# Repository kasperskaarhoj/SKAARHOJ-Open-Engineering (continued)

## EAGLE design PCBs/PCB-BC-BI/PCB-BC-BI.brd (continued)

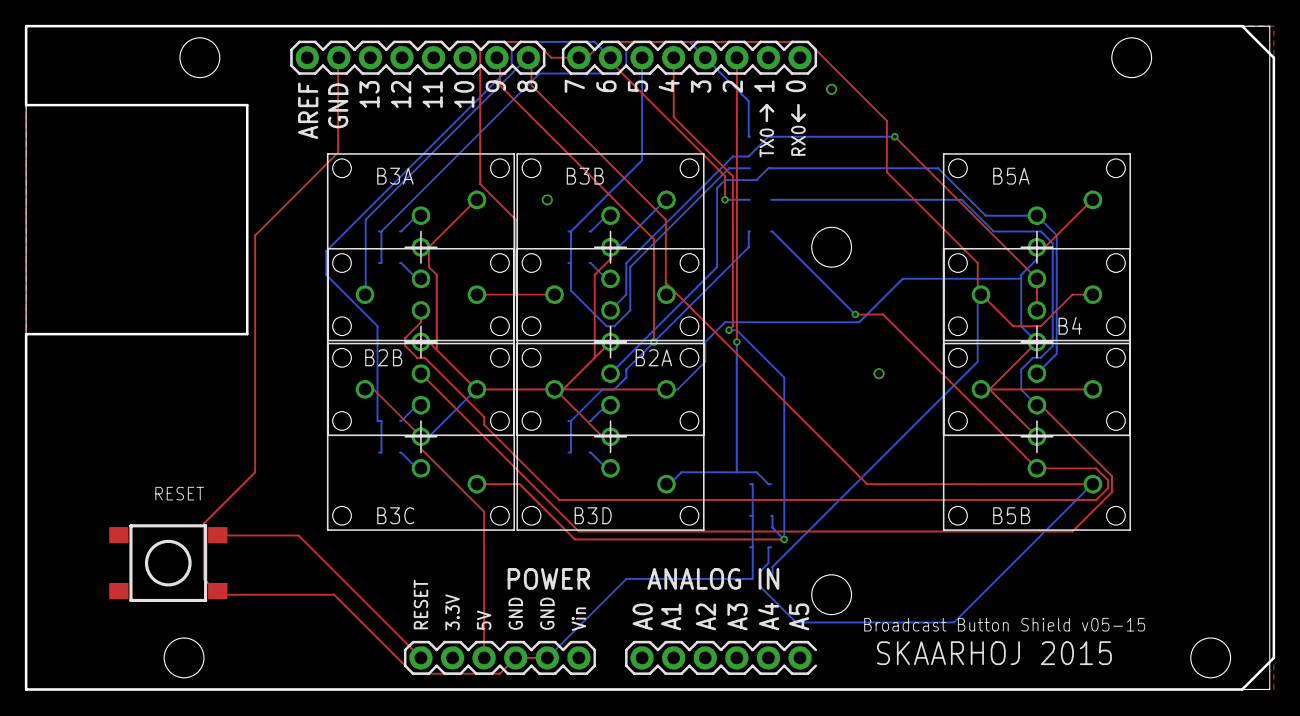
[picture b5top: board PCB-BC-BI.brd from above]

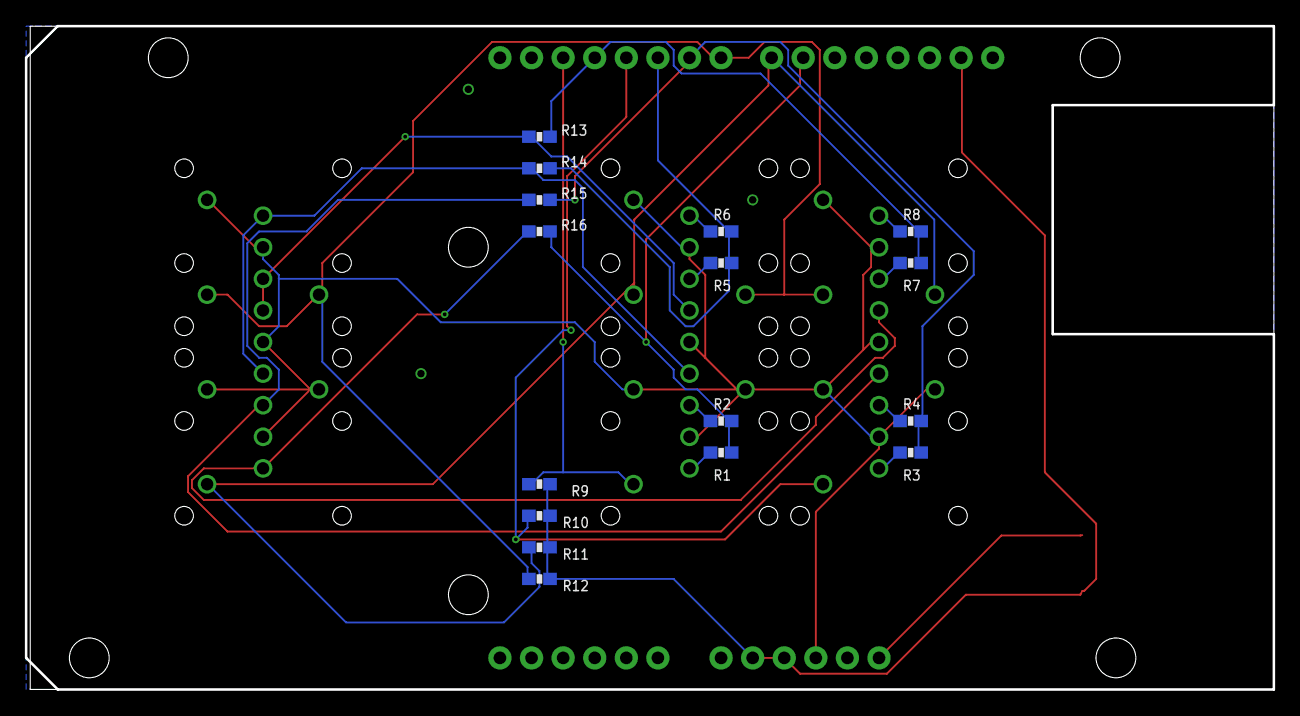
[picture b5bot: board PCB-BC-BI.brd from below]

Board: 2 copper layers, 100.3 x 53.3 mm, 27 parts (16 on the bottom side), 23 nets.

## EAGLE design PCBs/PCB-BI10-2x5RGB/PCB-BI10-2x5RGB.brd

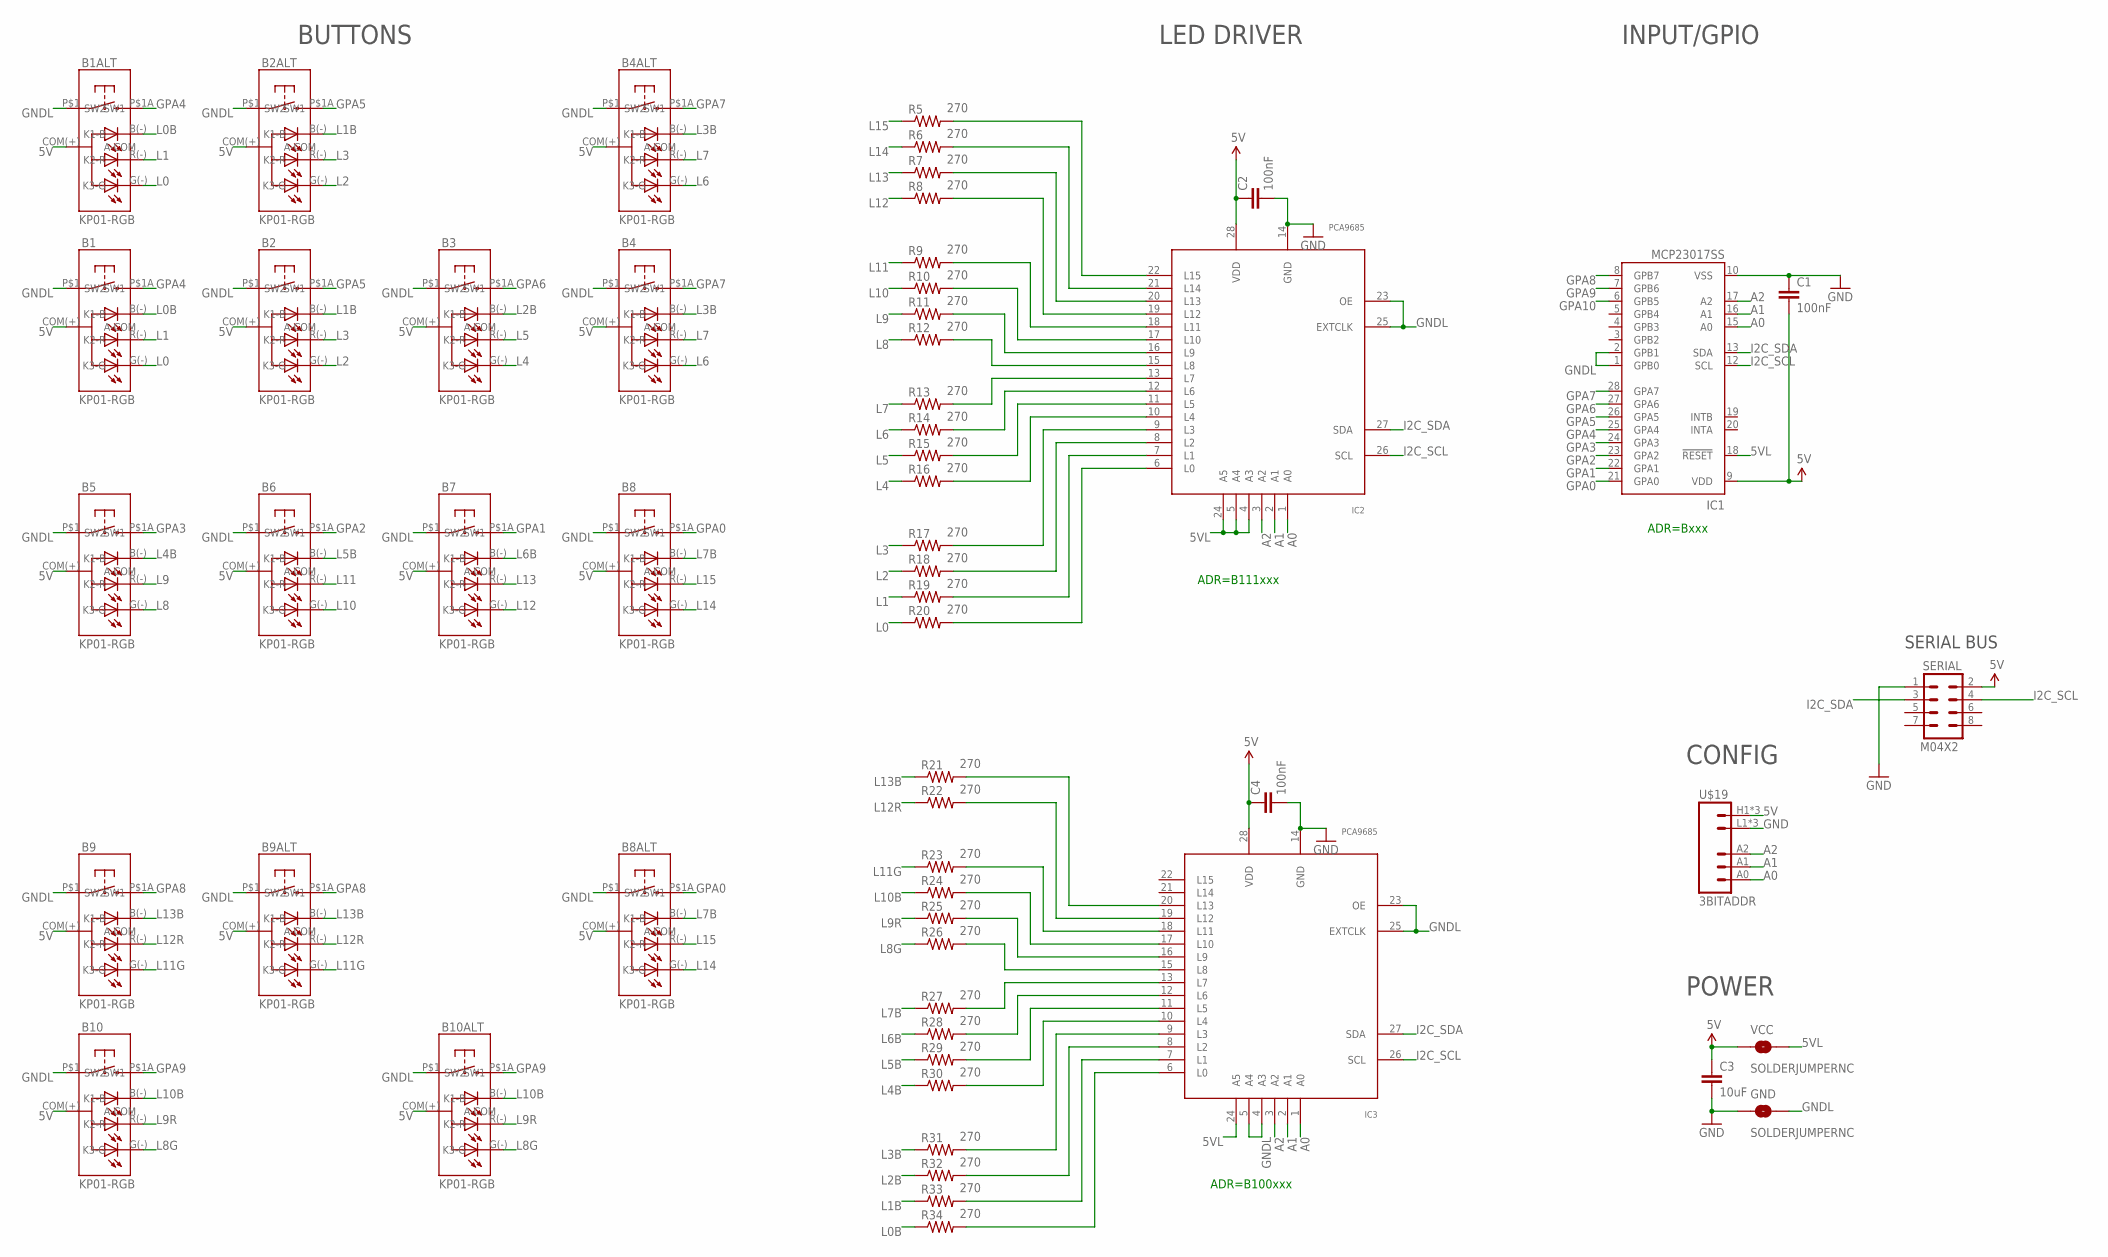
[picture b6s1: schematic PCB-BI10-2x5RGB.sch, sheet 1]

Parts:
B1, B1ALT, B2, B2ALT, B3, B4, B4ALT, B5, B6, B7, B8, B8ALT, B9, B9ALT, B10, B10ALT: KP01-RGB; NKK-KP01
C1, C2, C4: 100nF; 0603-CAP
C3: 10uF; 0805
GND: SOLDERJUMPERNC; SJ_2S
IC1: MCP23017SS; SSOP28; MPN MCP23017-E/SS
IC2, IC3: PCA9685; TSSOP28
R5, R6, R7, R8, R9, R10, R11, R12, R13, R14, R15, R16, R17, R18, R19, R20, R21, R22, R23, R24, R25, R26, R27, R28, R29, R30, R31, R32, R33, R34: 270; 0603-RES
SERIAL: M04X2; 2X4
U$19: 3BITADDR
VCC: SOLDERJUMPERNC; SJ_2S

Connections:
5V: B1.COM(+) (A-COM), B1ALT.COM(+) (A-COM), B2.COM(+) (A-COM), B2ALT.COM(+) (A-COM), B3.COM(+) (A-COM), B4.COM(+) (A-COM), B4ALT.COM(+) (A-COM), B5.COM(+) (A-COM), B6.COM(+) (A-COM), B7.COM(+) (A-COM), B8.COM(+) (A-COM), B8ALT.COM(+) (A-COM), B9.COM(+) (A-COM), B9ALT.COM(+) (A-COM), B10.COM(+) (A-COM), B10ALT.COM(+) (A-COM), C1.2, C2.1, C3.1, C4.1, IC1.9 (VDD), IC2.28 (VDD), IC3.28 (VDD), SERIAL.2, U$19.H1 (VCC), U$19.H2 (VCC), U$19.H3 (VCC), VCC.1
5VL: IC1.18 (!RESET), IC2.4 (A3), IC2.5 (A4), IC2.24 (A5), IC3.24 (A5), VCC.2
A0: IC1.15 (A0), IC2.1 (A0), IC3.1 (A0), U$19.A0
A1: IC1.16 (A1), IC2.2 (A1), IC3.2 (A1), U$19.A1
A2: IC1.17 (A2), IC2.3 (A2), IC3.3 (A2), U$19.A2
GND: C1.1, C2.2, C3.2, C4.2, GND.1, IC1.10 (VSS), IC2.14 (GND), IC3.14 (GND), SERIAL.1, U$19.L1 (GND), U$19.L2 (GND), U$19.L3 (GND)
GNDL: B1.P$1 (SW1), B1ALT.P$1 (SW1), B2.P$1 (SW1), B2ALT.P$1 (SW1), B3.P$1 (SW1), B4.P$1 (SW1), B4ALT.P$1 (SW1), B5.P$1 (SW1), B6.P$1 (SW1), B7.P$1 (SW1), B8.P$1 (SW1), B8ALT.P$1 (SW1), B9.P$1 (SW1), B9ALT.P$1 (SW1), B10.P$1 (SW1), B10ALT.P$1 (SW1), GND.2, IC1.1 (GPB0), IC1.2 (GPB1), IC2.23 (OE), IC2.25 (EXTCLK), IC3.4 (A3), IC3.5 (A4), IC3.23 (OE), IC3.25 (EXTCLK)
GPA0: B8.P$1A (SW2), B8ALT.P$1A (SW2), IC1.21 (GPA0)
GPA1: B7.P$1A (SW2), IC1.22 (GPA1)
GPA2: B6.P$1A (SW2), IC1.23 (GPA2)
GPA3: B5.P$1A (SW2), IC1.24 (GPA3)
GPA4: B1.P$1A (SW2), B1ALT.P$1A (SW2), IC1.25 (GPA4)
GPA5: B2.P$1A (SW2), B2ALT.P$1A (SW2), IC1.26 (GPA5)
GPA6: B3.P$1A (SW2), IC1.27 (GPA6)
GPA7: B4.P$1A (SW2), B4ALT.P$1A (SW2), IC1.28 (GPA7)
GPA8: B9.P$1A (SW2), B9ALT.P$1A (SW2), IC1.8 (GPB7)
GPA9: B10.P$1A (SW2), B10ALT.P$1A (SW2), IC1.7 (GPB6)
GPA10: IC1.6 (GPB5)
I2C_SCL: IC1.12 (SCL), IC2.26 (SCL), IC3.26 (SCL), SERIAL.4
I2C_SDA: IC1.13 (SDA), IC2.27 (SDA), IC3.27 (SDA), SERIAL.3
L0: B1.G(-) (K3-G), B1ALT.G(-) (K3-G), R20.1
L0B: B1.B(-) (K1-B), B1ALT.B(-) (K1-B), R34.1
L1: B1.R(-) (K2-R), B1ALT.R(-) (K2-R), R19.1
L1B: B2.B(-) (K1-B), B2ALT.B(-) (K1-B), R33.1
L2: B2.G(-) (K3-G), B2ALT.G(-) (K3-G), R18.1
L2B: B3.B(-) (K1-B), R32.1
L3: B2.R(-) (K2-R), B2ALT.R(-) (K2-R), R17.1
L3B: B4.B(-) (K1-B), B4ALT.B(-) (K1-B), R31.1
L4: B3.G(-) (K3-G), R16.1
L4B: B5.B(-) (K1-B), R30.1
L5: B3.R(-) (K2-R), R15.1
L5B: B6.B(-) (K1-B), R29.1
L6: B4.G(-) (K3-G), B4ALT.G(-) (K3-G), R14.1
L6B: B7.B(-) (K1-B), R28.1
L7: B4.R(-) (K2-R), B4ALT.R(-) (K2-R), R13.1
L7B: B8.B(-) (K1-B), B8ALT.B(-) (K1-B), R27.1
L8: B5.G(-) (K3-G), R12.1
L8G: B10.G(-) (K3-G), B10ALT.G(-) (K3-G), R26.1
L9: B5.R(-) (K2-R), R11.1
L9R: B10.R(-) (K2-R), B10ALT.R(-) (K2-R), R25.1
L10: B6.G(-) (K3-G), R10.1
L10B: B10.B(-) (K1-B), B10ALT.B(-) (K1-B), R24.1
L11: B6.R(-) (K2-R), R9.1
L11G: B9.G(-) (K3-G), B9ALT.G(-) (K3-G), R23.1
L12: B7.G(-) (K3-G), R8.1
L12R: B9.R(-) (K2-R), B9ALT.R(-) (K2-R), R22.1
L13: B7.R(-) (K2-R), R7.1
L13B: B9.B(-) (K1-B), B9ALT.B(-) (K1-B), R21.1
L14: B8.G(-) (K3-G), B8ALT.G(-) (K3-G), R6.1
L15: B8.R(-) (K2-R), B8ALT.R(-) (K2-R), R5.1
unnamed: IC3.13 (L7), R27.2
unnamed: IC3.12 (L6), R28.2
unnamed: IC2.13 (L7), R13.2
unnamed: IC2.12 (L6), R14.2
unnamed: IC3.11 (L5), R29.2
unnamed: IC2.11 (L5), R15.2
unnamed: IC2.10 (L4), R16.2
unnamed: IC2.9 (L3), R17.2
unnamed: IC2.8 (L2), R18.2
unnamed: IC2.7 (L1), R19.2
unnamed: IC3.10 (L4), R30.2
unnamed: IC3.9 (L3), R31.2
unnamed: IC3.8 (L2), R32.2
unnamed: IC3.7 (L1), R33.2
unnamed: IC3.6 (L0), R34.2
unnamed: IC3.15 (L8), R26.2
unnamed: IC2.6 (L0), R20.2
unnamed: IC2.15 (L8), R12.2
unnamed: IC2.16 (L9), R11.2
unnamed: IC2.17 (L10), R10.2
unnamed: IC2.18 (L11), R9.2
unnamed: IC2.19 (L12), R8.2
unnamed: IC2.20 (L13), R7.2
unnamed: IC2.21 (L14), R6.2
unnamed: IC2.22 (L15), R5.2
unnamed: IC3.16 (L9), R25.2
unnamed: IC3.17 (L10), R24.2
unnamed: IC3.18 (L11), R23.2
unnamed: IC3.19 (L12), R22.2
unnamed: IC3.20 (L13), R21.2

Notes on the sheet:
SERIAL BUS
ADR=B111xxx
ADR=Bxxx
BUTTONS
LED DRIVER
INPUT/GPIO
POWER
ADR=B100xxx
CONFIG

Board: 2 copper layers, 57 parts (41 on the bottom side), 79 nets, no tracks yet.

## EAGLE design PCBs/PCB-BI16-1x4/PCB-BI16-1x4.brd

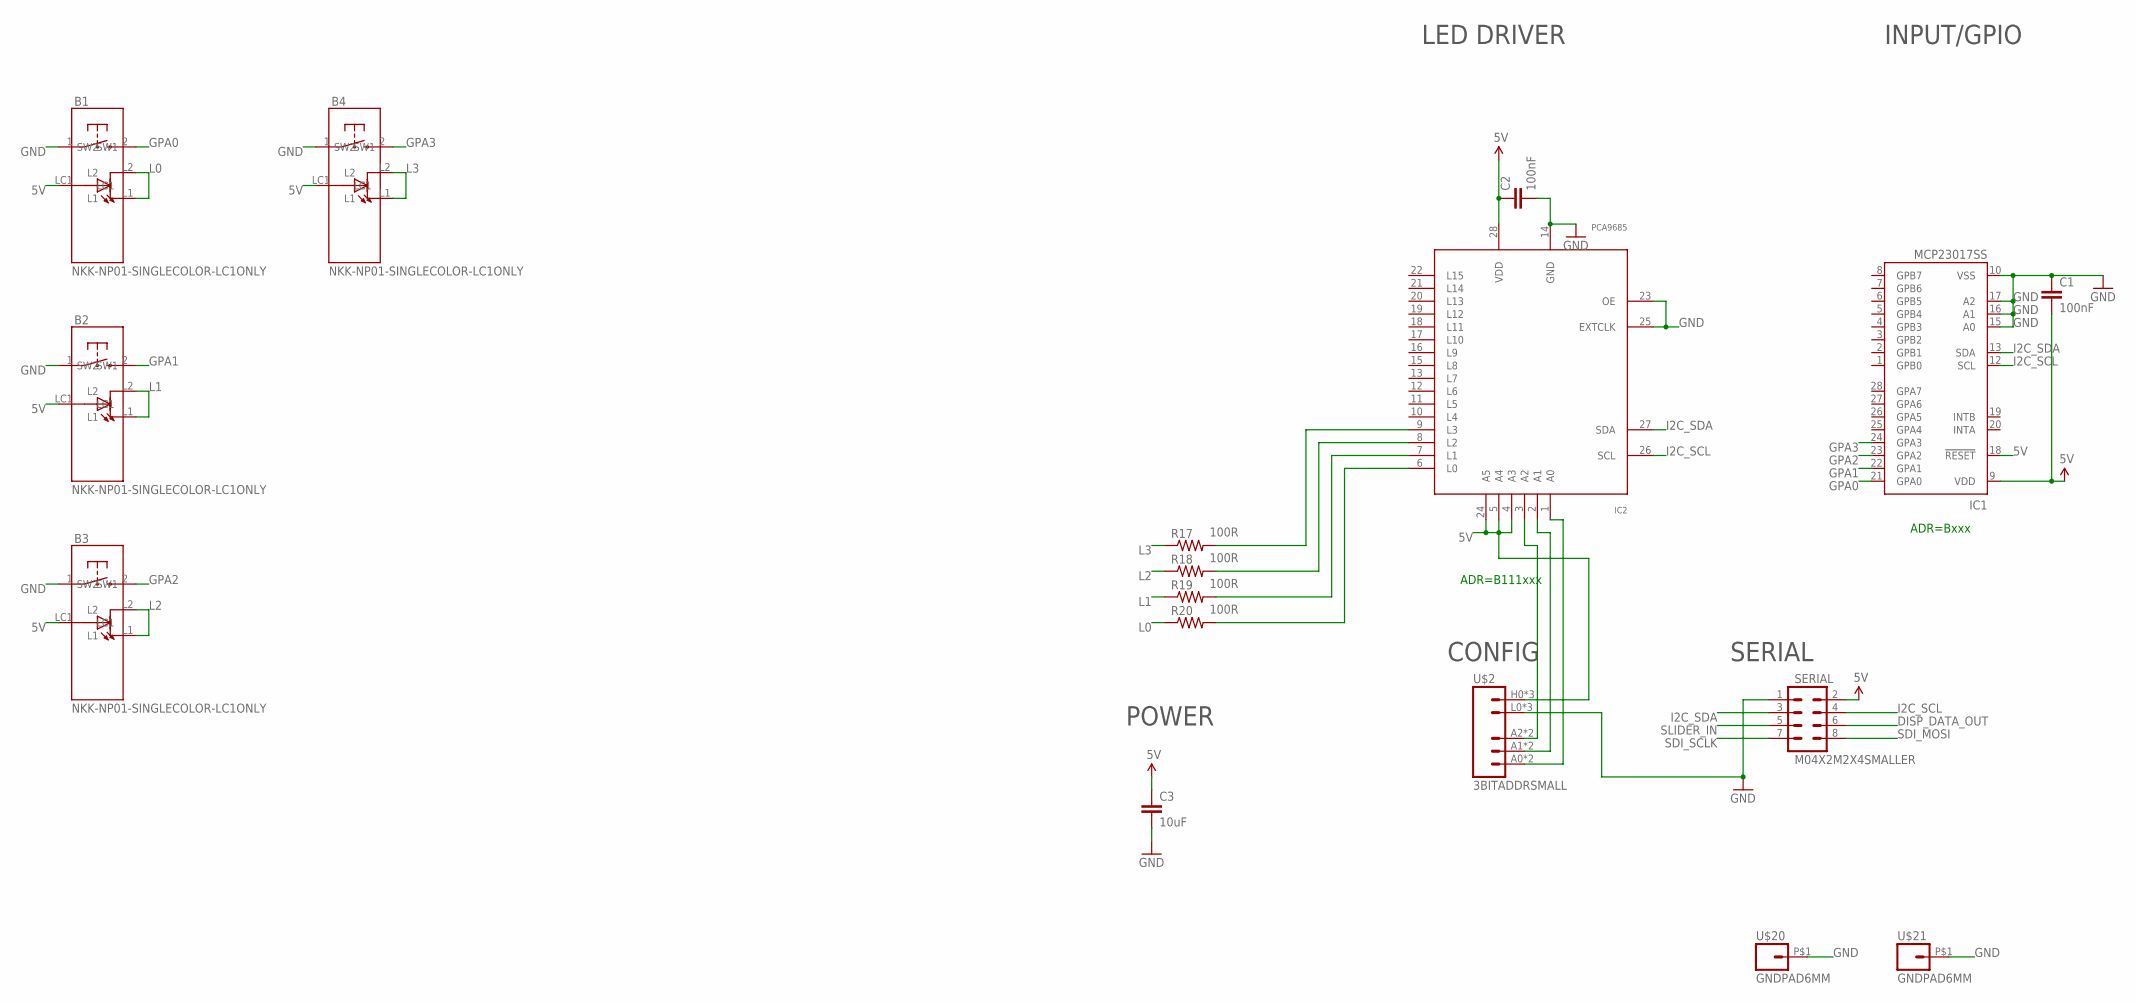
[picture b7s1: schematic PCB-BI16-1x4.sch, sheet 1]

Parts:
B1, B2, B3, B4: NKK-NP01-SINGLECOLOR-LC1ONLY; NKK-NP01_LESSHOLES2
C1, C2: 100nF; 0603-CAP
C3: 10uF; 0805
IC1: MCP23017SS; SSOP28; MPN MCP23017-E/SS
IC2: PCA9685; TSSOP28
R17, R18, R19, R20: 100R; 0603-RES
SERIAL: M04X2M2X4SMALLER; M2X4SMALLER
U$2: 3BITADDRSMALL; 3BITADDR_SMALL
U$20, U$21: GNDPAD6MM; 3.2MMPAD6MM

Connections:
5V: B1.LC1, B2.LC1, B3.LC1, B4.LC1, C1.2, C2.1, C3.1, IC1.9 (VDD), IC1.18 (!RESET), IC2.4 (A3), IC2.5 (A4), IC2.24 (A5), IC2.28 (VDD), SERIAL.2, U$2.H0 (VCC), U$2.H1 (VCC), U$2.H2 (VCC)
DISP_DATA_OUT: SERIAL.6
GND: B1.1 (SW1), B2.1 (SW1), B3.1 (SW1), B4.1 (SW1), C1.1, C2.2, C3.2, IC1.10 (VSS), IC1.15 (A0), IC1.16 (A1), IC1.17 (A2), IC2.14 (GND), IC2.23 (OE), IC2.25 (EXTCLK), SERIAL.1, U$2.L0 (GND), U$2.L1 (GND), U$2.L2 (GND), U$20.P$1, U$21.P$1
GPA0: B1.2 (SW2), IC1.21 (GPA0)
GPA1: B2.2 (SW2), IC1.22 (GPA1)
GPA2: B3.2 (SW2), IC1.23 (GPA2)
GPA3: B4.2 (SW2), IC1.24 (GPA3)
I2C_SCL: IC1.12 (SCL), IC2.26 (SCL), SERIAL.4
I2C_SDA: IC1.13 (SDA), IC2.27 (SDA), SERIAL.3
L0: B1.L1, B1.L2, R20.1
L1: B2.L1, B2.L2, R19.1
L2: B3.L1, B3.L2, R18.1
L3: B4.L1, B4.L2, R17.1
unnamed: IC2.3 (A2), U$2.A2, U$2.AS2 (A2)
unnamed: IC2.2 (A1), U$2.A1, U$2.AS1 (A1)
unnamed: IC2.1 (A0), U$2.A0, U$2.AS0 (A0)
unnamed: IC2.9 (L3), R17.2
unnamed: IC2.8 (L2), R18.2
unnamed: IC2.7 (L1), R19.2
unnamed: IC2.6 (L0), R20.2
SDI_MOSI: SERIAL.8
SDI_SCLK: SERIAL.7
SLIDER_IN: SERIAL.5

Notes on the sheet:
ADR=B111xxx
ADR=Bxxx
LED DRIVER
INPUT/GPIO
POWER
SERIAL
CONFIG

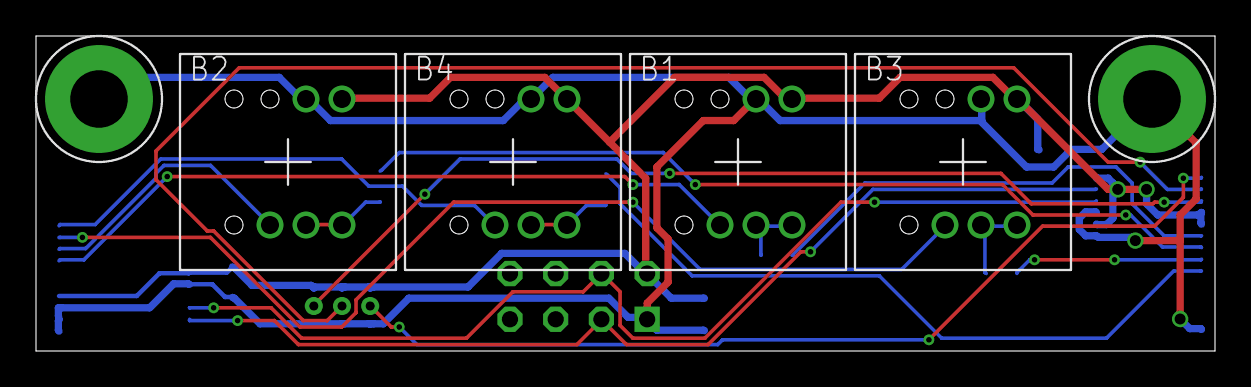
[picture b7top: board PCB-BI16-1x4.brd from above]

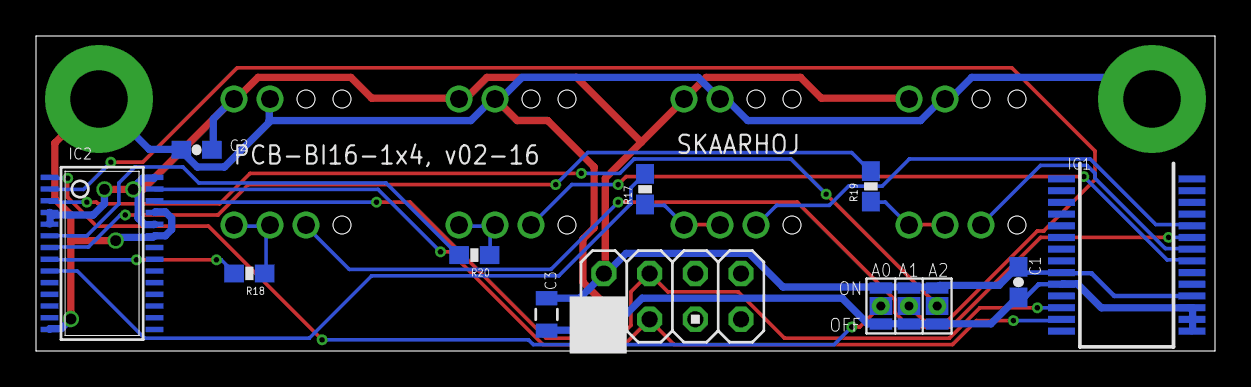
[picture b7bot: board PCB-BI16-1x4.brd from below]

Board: 2 copper layers, 65.5 x 17.5 mm, 17 parts (11 on the bottom side), 19 nets.

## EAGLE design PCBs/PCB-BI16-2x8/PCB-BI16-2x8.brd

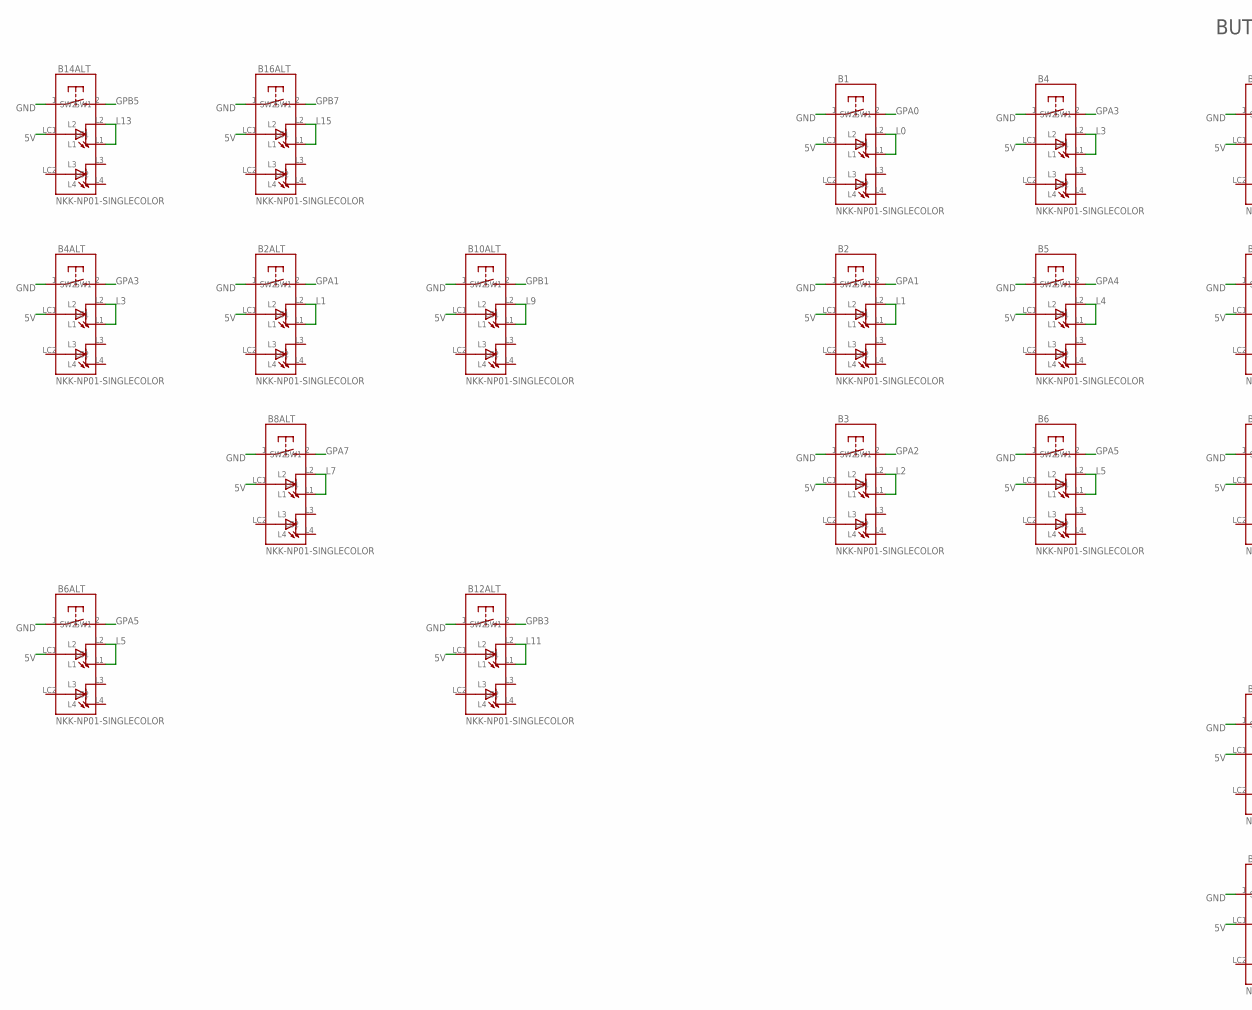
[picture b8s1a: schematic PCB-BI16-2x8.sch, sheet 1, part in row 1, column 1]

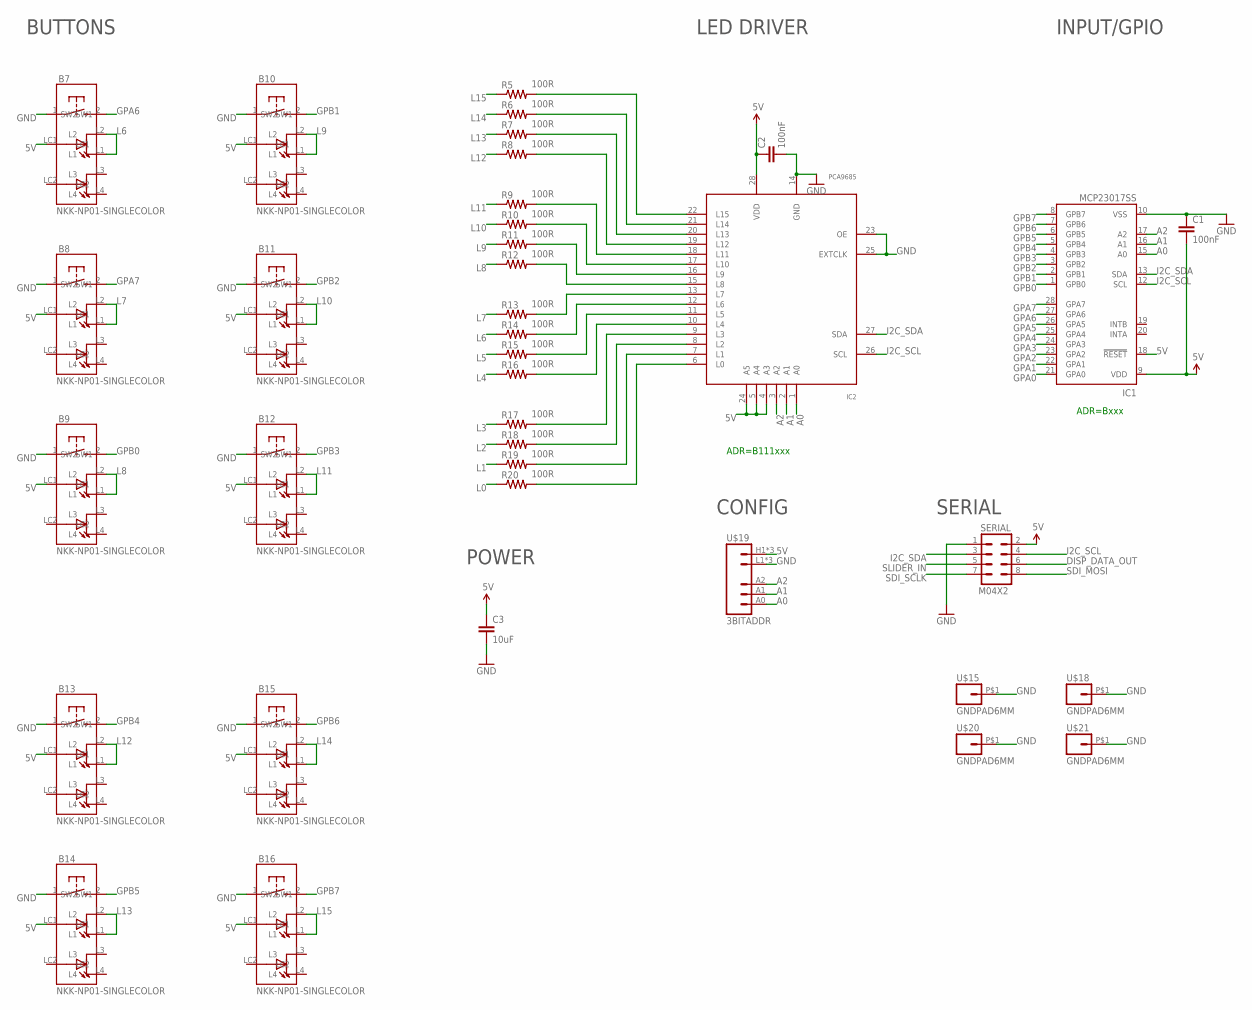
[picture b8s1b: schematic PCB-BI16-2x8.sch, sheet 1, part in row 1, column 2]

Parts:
B1, B2, B2ALT, B3, B4, B4ALT, B5, B6, B6ALT, B7, B8, B8ALT, B9, B10, B10ALT, B11, B12, B12ALT, B13, B14, B14ALT, B15, B16, B16ALT: NKK-NP01-SINGLECOLOR; NKK-NP01
C1, C2: 100nF; 0603-CAP
C3: 10uF; 0805
IC1: MCP23017SS; SSOP28; MPN MCP23017-E/SS
IC2: PCA9685; TSSOP28
R5, R6, R7, R8, R9, R10, R11, R12, R13, R14, R15, R16, R17, R18, R19, R20: 100R; 0603-RES
SERIAL: M04X2; 2X4
U$15, U$18, U$20, U$21: GNDPAD6MM; 3.2MMPAD6MM
U$19: 3BITADDR

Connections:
5V: B1.LC1, B2.LC1, B2ALT.LC1, B3.LC1, B4.LC1, B4ALT.LC1, B5.LC1, B6.LC1, B6ALT.LC1, B7.LC1, B8.LC1, B8ALT.LC1, B9.LC1, B10.LC1, B10ALT.LC1, B11.LC1, B12.LC1, B12ALT.LC1, B13.LC1, B14.LC1, B14ALT.LC1, B15.LC1, B16.LC1, B16ALT.LC1, C1.2, C2.1, C3.1, IC1.9 (VDD), IC1.18 (!RESET), IC2.4 (A3), IC2.5 (A4), IC2.24 (A5), IC2.28 (VDD), SERIAL.2, U$19.H1 (VCC), U$19.H2 (VCC), U$19.H3 (VCC)
A0: IC1.15 (A0), IC2.1 (A0), U$19.A0
A1: IC1.16 (A1), IC2.2 (A1), U$19.A1
A2: IC1.17 (A2), IC2.3 (A2), U$19.A2
DISP_DATA_OUT: SERIAL.6
GND: B1.1 (SW1), B2.1 (SW1), B2ALT.1 (SW1), B3.1 (SW1), B4.1 (SW1), B4ALT.1 (SW1), B5.1 (SW1), B6.1 (SW1), B6ALT.1 (SW1), B7.1 (SW1), B8.1 (SW1), B8ALT.1 (SW1), B9.1 (SW1), B10.1 (SW1), B10ALT.1 (SW1), B11.1 (SW1), B12.1 (SW1), B12ALT.1 (SW1), B13.1 (SW1), B14.1 (SW1), B14ALT.1 (SW1), B15.1 (SW1), B16.1 (SW1), B16ALT.1 (SW1), C1.1, C2.2, C3.2, IC1.10 (VSS), IC2.14 (GND), IC2.23 (OE), IC2.25 (EXTCLK), SERIAL.1, U$15.P$1, U$18.P$1, U$19.L1 (GND), U$19.L2 (GND), U$19.L3 (GND), U$20.P$1, U$21.P$1
GPA0: B1.2 (SW2), IC1.21 (GPA0)
GPA1: B2.2 (SW2), B2ALT.2 (SW2), IC1.22 (GPA1)
GPA2: B3.2 (SW2), IC1.23 (GPA2)
GPA3: B4.2 (SW2), B4ALT.2 (SW2), IC1.24 (GPA3)
GPA4: B5.2 (SW2), IC1.25 (GPA4)
GPA5: B6.2 (SW2), B6ALT.2 (SW2), IC1.26 (GPA5)
GPA6: B7.2 (SW2), IC1.27 (GPA6)
GPA7: B8.2 (SW2), B8ALT.2 (SW2), IC1.28 (GPA7)
GPB0: B9.2 (SW2), IC1.1 (GPB0)
GPB1: B10.2 (SW2), B10ALT.2 (SW2), IC1.2 (GPB1)
GPB2: B11.2 (SW2), IC1.3 (GPB2)
GPB3: B12.2 (SW2), B12ALT.2 (SW2), IC1.4 (GPB3)
GPB4: B13.2 (SW2), IC1.5 (GPB4)
GPB5: B14.2 (SW2), B14ALT.2 (SW2), IC1.6 (GPB5)
GPB6: B15.2 (SW2), IC1.7 (GPB6)
GPB7: B16.2 (SW2), B16ALT.2 (SW2), IC1.8 (GPB7)
I2C_SCL: IC1.12 (SCL), IC2.26 (SCL), SERIAL.4
I2C_SDA: IC1.13 (SDA), IC2.27 (SDA), SERIAL.3
L0: B1.L1, B1.L2, R20.1
L1: B2.L1, B2.L2, B2ALT.L1, B2ALT.L2, R19.1
L2: B3.L1, B3.L2, R18.1
L3: B4.L1, B4.L2, B4ALT.L1, B4ALT.L2, R17.1
L4: B5.L1, B5.L2, R16.1
L5: B6.L1, B6.L2, B6ALT.L1, B6ALT.L2, R15.1
L6: B7.L1, B7.L2, R14.1
L7: B8.L1, B8.L2, B8ALT.L1, B8ALT.L2, R13.1
L8: B9.L1, B9.L2, R12.1
L9: B10.L1, B10.L2, B10ALT.L1, B10ALT.L2, R11.1
L10: B11.L1, B11.L2, R10.1
L11: B12.L1, B12.L2, B12ALT.L1, B12ALT.L2, R9.1
L12: B13.L1, B13.L2, R8.1
L13: B14.L1, B14.L2, B14ALT.L1, B14ALT.L2, R7.1
L14: B15.L1, B15.L2, R6.1
L15: B16.L1, B16.L2, B16ALT.L1, B16ALT.L2, R5.1
unnamed: IC2.13 (L7), R13.2
unnamed: IC2.12 (L6), R14.2
unnamed: IC2.11 (L5), R15.2
unnamed: IC2.10 (L4), R16.2
unnamed: IC2.9 (L3), R17.2
unnamed: IC2.8 (L2), R18.2
unnamed: IC2.7 (L1), R19.2
unnamed: IC2.6 (L0), R20.2
unnamed: IC2.15 (L8), R12.2
unnamed: IC2.16 (L9), R11.2
unnamed: IC2.17 (L10), R10.2
unnamed: IC2.18 (L11), R9.2
unnamed: IC2.19 (L12), R8.2
unnamed: IC2.20 (L13), R7.2
unnamed: IC2.21 (L14), R6.2
unnamed: IC2.22 (L15), R5.2
SDI_MOSI: SERIAL.8
SDI_SCLK: SERIAL.7
SLIDER_IN: SERIAL.5

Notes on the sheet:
ADR=B111xxx
ADR=Bxxx
BUTTONS
LED DRIVER
INPUT/GPIO
POWER
SERIAL
CONFIG

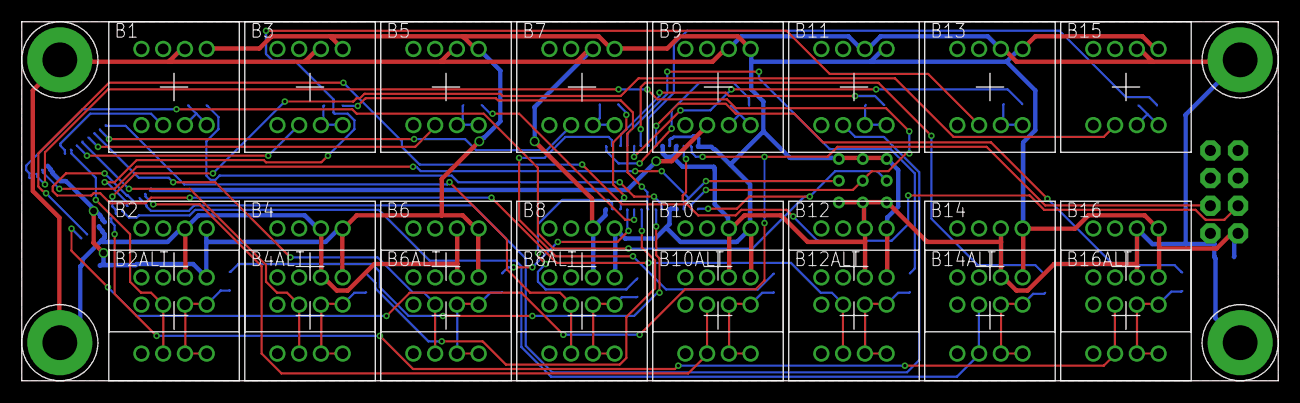
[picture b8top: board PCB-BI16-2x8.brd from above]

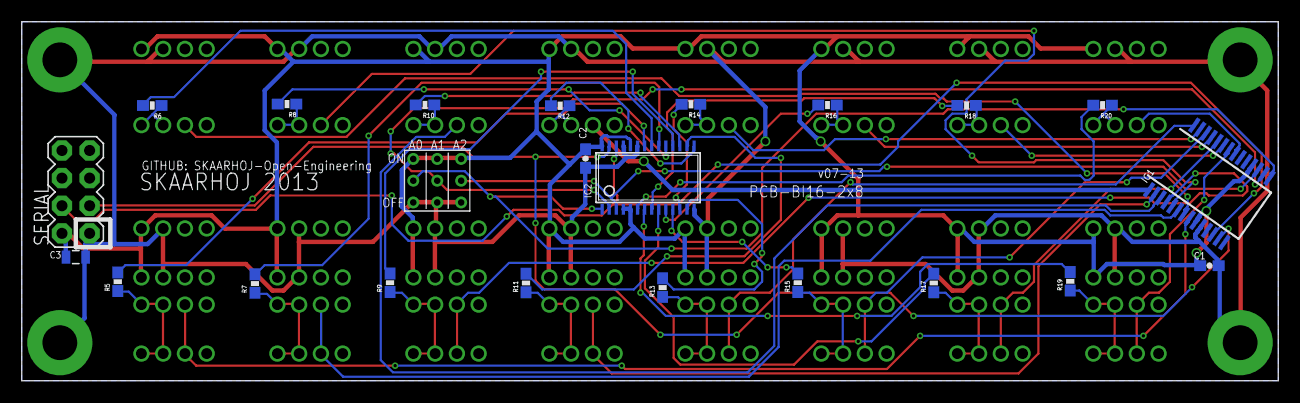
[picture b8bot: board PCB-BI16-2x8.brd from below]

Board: 2 copper layers, 115.5 x 33.0 mm, 51 parts (23 on the bottom side), 55 nets.
